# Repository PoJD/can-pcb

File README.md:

# can-pcb
Custom PCBs to be used for CAN bus in my home automation project
This repository contains 2 separate Eagle projects (http://www.cadsoftusa.com/) for custom PCB designed by myself to allow home automation system work with CAN BUS.

The basic idee is that there are 2 projects:

1. CanRelay
2. CanSwitch

CanRelay is a PCB that will be directly connected to the SSR relays and will consume traffic over the CAN bus (from either the webapp - hawa - or from CanSwitch) and translate that to switching output pins on that board's chip on or off. The board chip is PIC18F25K80 and is programmed through either CanRelay.X or CanSwitch.X mplab projects here: https://github.com/PoJD/can

CanSwitch is a PCB that will be present in the wall and would have 1 single input for the input switch, 1 single output for an indicator LED and would be connected to the CAN network too and transfer the toggle switch CAN messages over the wire to the CanRelay PCB to process.

Followed https://www.sparkfun.com/tutorials/110 to create custom components bought for this PCB and resulting in a custom library here: https://github.com/PoJD/eagle
Then followed https://learn.sparkfun.com/tutorials/using-eagle-schematic/adding-parts-to-a-schematic and other related guides to create the PCB in Eagle application.

https://learn.sparkfun.com/tutorials/using-eagle-board-layout#generating-gerbers and http://www.allpcb.com/sns/Gerber+File/2017-02-24_1_10_4819_Create+a+Gerber+File+with+Eagle/rpllst.html for generating Gerber files to let the PCBs get manufactured

See details of the communication protocal in that project, this is simply a project designed to have custom boards that would then be installed in the house.

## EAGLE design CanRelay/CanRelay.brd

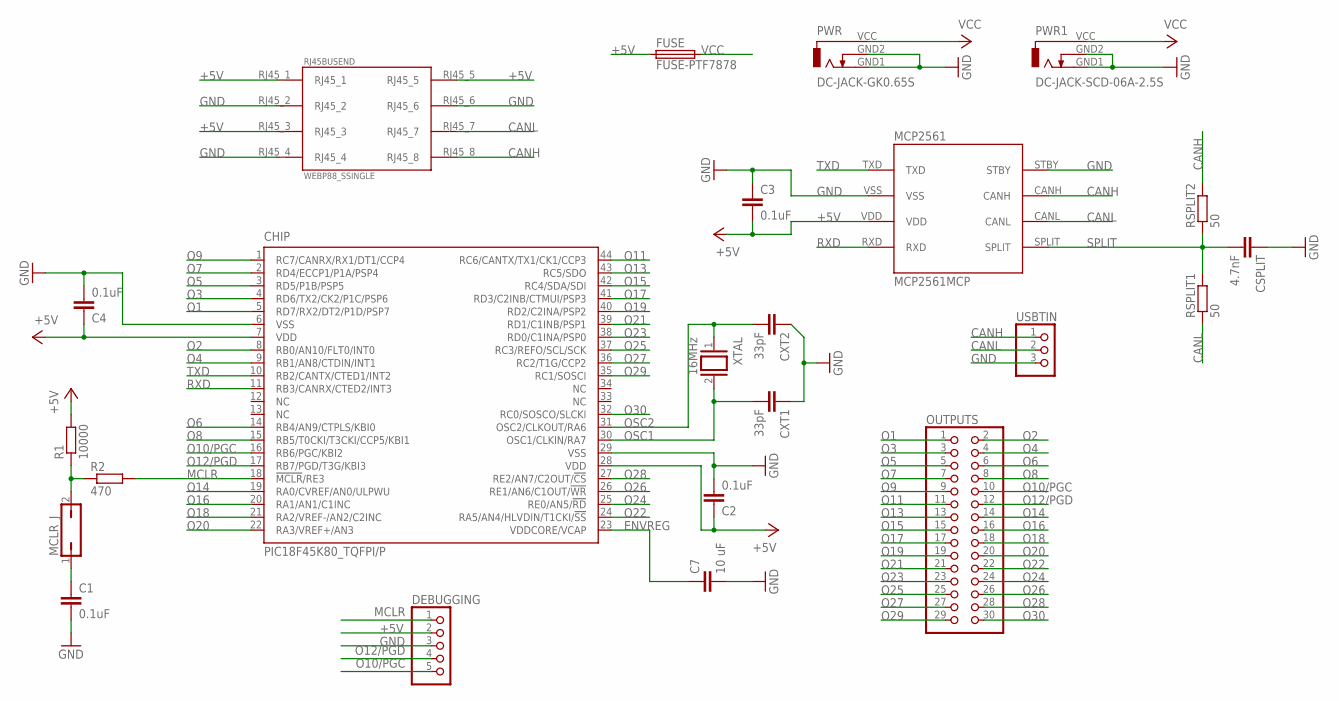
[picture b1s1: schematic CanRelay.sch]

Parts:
C1, C2, C3, C4: 0.1uF; C050-025X075
C7: 10 uF; C050-025X075
CHIP: PIC18F45K80_TQFPI/P; TQFP44
CSPLIT: 4.7nF; C050-025X075
CXT1, CXT2: 33pF; C025-030X050
DEBUGGING: PINHD-1X5; 1X05
FUSE: FUSE-PTF7878; FUSE-PTF78
MCLR_J: JP1Q; JP1
MCP2561: MCP2561MCP; MCP2561_PDIP
OUTPUTS: PINHD-2X15; 2X15
PWR: DC-JACK-GK0.65S; DC-JACK-GK0.65
PWR1: DC-JACK-SCD-06A-2.5S; DC-JACK-SCD-016A-2.5
R1: 10000; 0207/10
R2: 470; 0207/10
RJ45BUSEND: WEBP88_SSINGLE; WEBP88_RJ45_SINGLE
RSPLIT1, RSPLIT2: 50; 0207/10
USBTIN: PINHD-1X3; 1X03
XTAL: 16MHz; QS

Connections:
+5V: C2.1, C3.2, C4.1, CHIP.7 (VDD), CHIP.28 (VDD), DEBUGGING.2, FUSE.P1 (1), MCP2561.VDD, R1.2, RJ45BUSEND.RJ45_1, RJ45BUSEND.RJ45_3, RJ45BUSEND.RJ45_5
CANH: MCP2561.CANH, RJ45BUSEND.RJ45_8, RSPLIT2.2, USBTIN.1
CANL: MCP2561.CANL, RJ45BUSEND.RJ45_7, RSPLIT1.1, USBTIN.2
ENVREG: C7.1, CHIP.23 (VDDCORE/VCAP)
GND: C1.2, C2.2, C3.1, C4.2, C7.2, CHIP.6 (VSS), CHIP.29 (VSS), CSPLIT.1, CXT1.1, CXT2.1, DEBUGGING.3, MCP2561.STBY, MCP2561.VSS, PWR.GND1, PWR.GND2, PWR1.GND1, PWR1.GND2, RJ45BUSEND.RJ45_2, RJ45BUSEND.RJ45_4, RJ45BUSEND.RJ45_6, USBTIN.3
MCLR: CHIP.18 (!MCLR!/RE3), DEBUGGING.1, R2.2
unnamed: C1.1, MCLR_J.1
unnamed: MCLR_J.2, R1.1, R2.1
O1: CHIP.5 (RD7/RX2/DT2/P1D/PSP7), OUTPUTS.1
O2: CHIP.8 (RB0/AN10/FLT0/INT0), OUTPUTS.2
O3: CHIP.4 (RD6/TX2/CK2/P1C/PSP6), OUTPUTS.3
O4: CHIP.9 (RB1/AN8/CTDIN/INT1), OUTPUTS.4
O5: CHIP.3 (RD5/P1B/PSP5), OUTPUTS.5
O6: CHIP.14 (RB4/AN9/CTPLS/KBI0), OUTPUTS.6
O7: CHIP.2 (RD4/ECCP1/P1A/PSP4), OUTPUTS.7
O8: CHIP.15 (RB5/T0CKI/T3CKI/CCP5/KBI1), OUTPUTS.8
O9: CHIP.1 (RC7/CANRX/RX1/DT1/CCP4), OUTPUTS.9
O10/PGC: CHIP.16 (RB6/PGC/KBI2), DEBUGGING.5, OUTPUTS.10
O11: CHIP.44 (RC6/CANTX/TX1/CK1/CCP3), OUTPUTS.11
O12/PGD: CHIP.17 (RB7/PGD/T3G/KBI3), DEBUGGING.4, OUTPUTS.12
O13: CHIP.43 (RC5/SDO), OUTPUTS.13
O14: CHIP.19 (RA0/CVREF/AN0/ULPWU), OUTPUTS.14
O15: CHIP.42 (RC4/SDA/SDI), OUTPUTS.15
O16: CHIP.20 (RA1/AN1/C1INC), OUTPUTS.16
O17: CHIP.41 (RD3/C2INB/CTMUI/PSP3), OUTPUTS.17
O18: CHIP.21 (RA2/VREF-/AN2/C2INC), OUTPUTS.18
O19: CHIP.40 (RD2/C2INA/PSP2), OUTPUTS.19
O20: CHIP.22 (RA3/VREF+/AN3), OUTPUTS.20
O21: CHIP.39 (RD1/C1INB/PSP1), OUTPUTS.21
O22: CHIP.24 (RA5/AN4/HLVDIN/T1CKI/!SS!), OUTPUTS.22
O23: CHIP.38 (RD0/C1INA/PSP0), OUTPUTS.23
O24: CHIP.25 (RE0/AN5/!RD!), OUTPUTS.24
O25: CHIP.37 (RC3/REFO/SCL/SCK), OUTPUTS.25
O26: CHIP.26 (RE1/AN6/C1OUT/!WR!), OUTPUTS.26
O27: CHIP.36 (RC2/T1G/CCP2), OUTPUTS.27
O28: CHIP.27 (RE2/AN7/C2OUT/!CS!), OUTPUTS.28
O29: CHIP.35 (RC1/SOSCI), OUTPUTS.29
O30: CHIP.32 (RC0/SOSCO/SLCKI), OUTPUTS.30
OSC1: CHIP.30 (OSC1/CLKIN/RA7), CXT1.2, XTAL.2
OSC2: CHIP.31 (OSC2/CLKOUT/RA6), CXT2.2, XTAL.1
RXD: CHIP.11 (RB3/CANRX/CTED2/INT3), MCP2561.RXD
SPLIT: CSPLIT.2, MCP2561.SPLIT, RSPLIT1.2, RSPLIT2.1
TXD: CHIP.10 (RB2/CANTX/CTED1/INT2), MCP2561.TXD
VCC: FUSE.P2 (2), PWR.VCC, PWR1.VCC

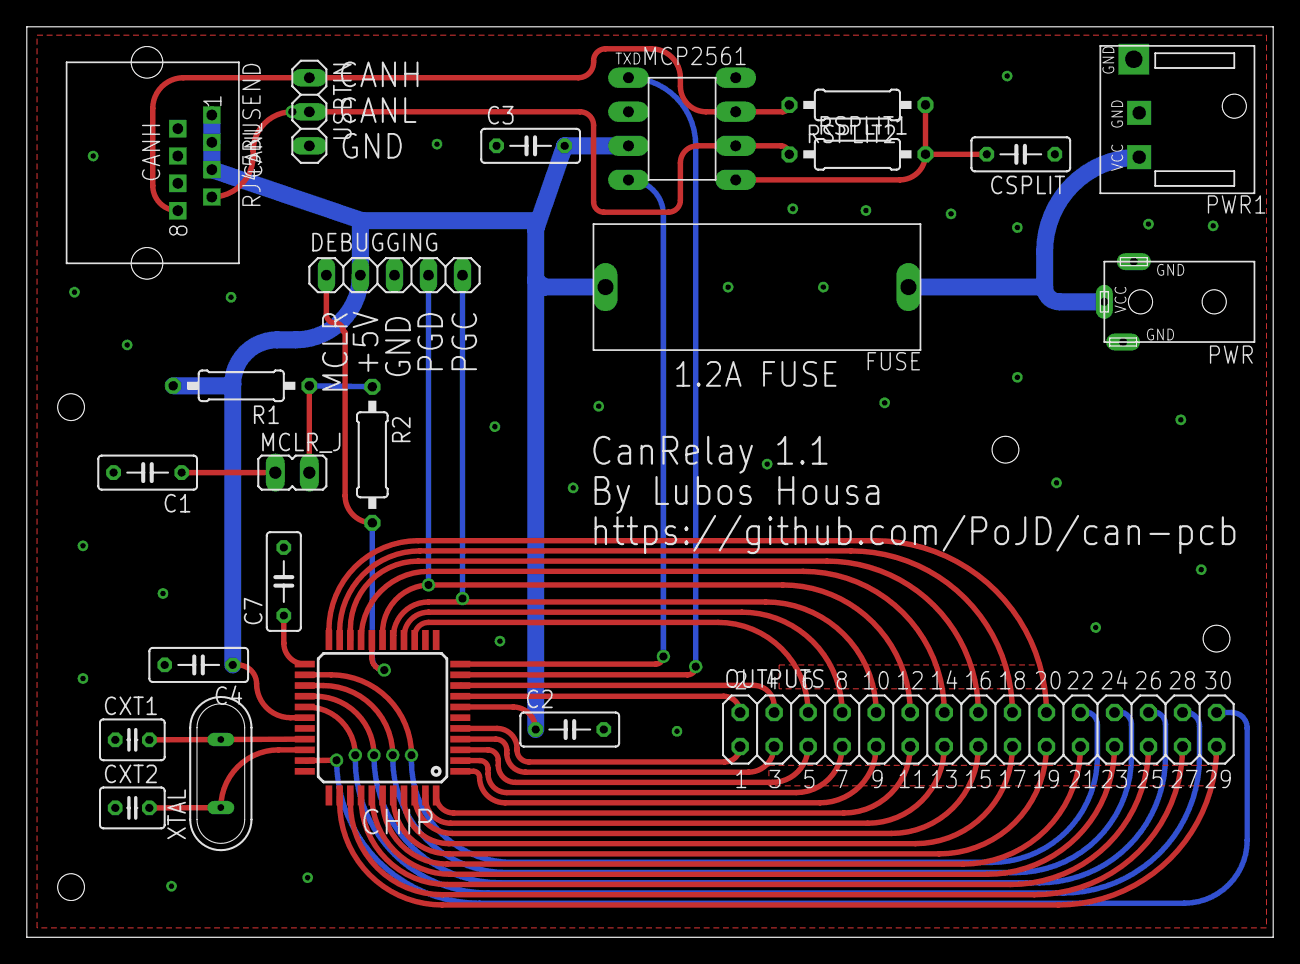
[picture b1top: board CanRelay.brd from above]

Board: 2 copper layers, 92.9 x 67.8 mm, 23 parts (0 on the bottom side), 44 nets.

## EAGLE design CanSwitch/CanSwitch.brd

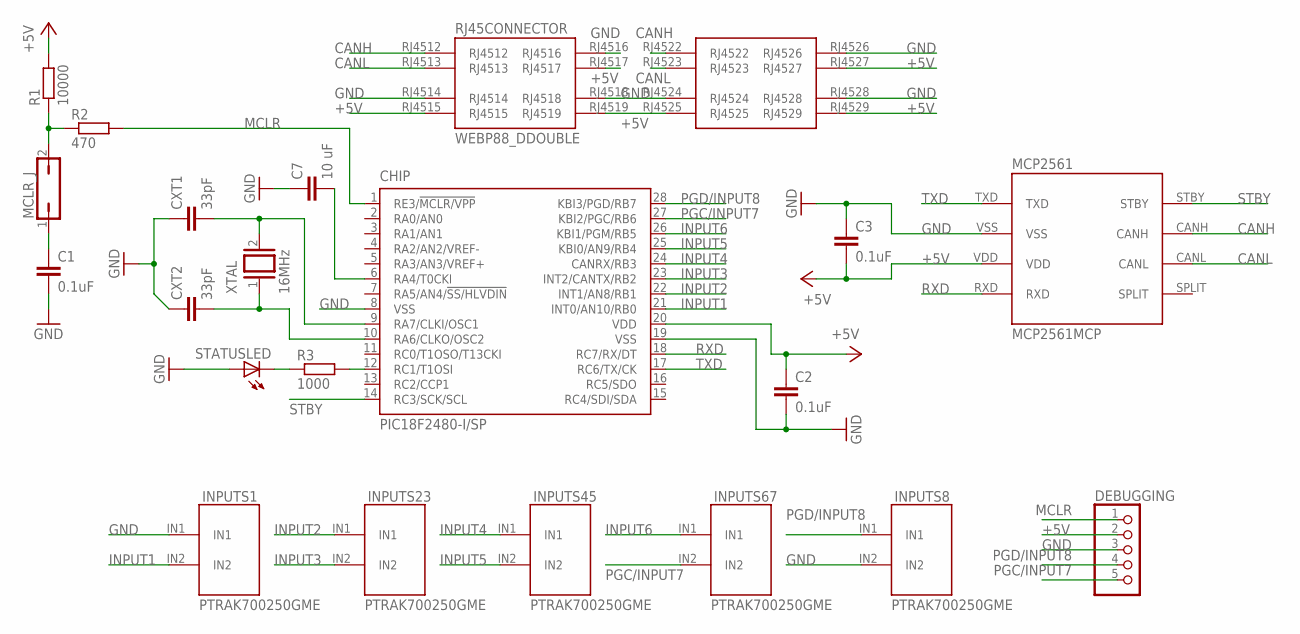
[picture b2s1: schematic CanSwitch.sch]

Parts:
C1: 0.1uF; C025-025X050
C2, C3: 0.1uF; C050-025X075
C7: 10 uF; C050-025X075
CHIP: PIC18F2480-I/SP; DIL28-3
CXT1, CXT2: 33pF; C025-030X050
DEBUGGING: PINHD-1X5; 1X05
INPUTS1, INPUTS8, INPUTS23, INPUTS45, INPUTS67: PTRAK700250GME; PTR_AK700_2_5.0
MCLR_J: JP1Q; JP1
MCP2561: MCP2561MCP; MCP2561_PDIP
R1: 10000; 0207/10
R2: 470; 0207/10
R3: 1000; 0207/10
RJ45CONNECTOR: WEBP88_DDOUBLE; WEBP88_RJ45_DOUBLE
STATUSLED: LED5MM
XTAL: 16MHz; QS

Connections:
+5V: C2.1, C3.2, CHIP.20 (VDD), DEBUGGING.2, MCP2561.VDD, R1.2, RJ45CONNECTOR.RJ4515, RJ45CONNECTOR.RJ4517, RJ45CONNECTOR.RJ4519, RJ45CONNECTOR.RJ4525, RJ45CONNECTOR.RJ4527, RJ45CONNECTOR.RJ4529
CANH: MCP2561.CANH, RJ45CONNECTOR.RJ4512, RJ45CONNECTOR.RJ4522
CANL: MCP2561.CANL, RJ45CONNECTOR.RJ4513, RJ45CONNECTOR.RJ4523
GND: C1.2, C2.2, C3.1, C7.1, CHIP.8 (VSS), CHIP.19 (VSS), CXT1.1, CXT2.1, DEBUGGING.3, INPUTS1.IN1, INPUTS8.IN2, MCP2561.VSS, RJ45CONNECTOR.RJ4514, RJ45CONNECTOR.RJ4516, RJ45CONNECTOR.RJ4518, RJ45CONNECTOR.RJ4524, RJ45CONNECTOR.RJ4526, RJ45CONNECTOR.RJ4528, STATUSLED.A
INPUT1: CHIP.21 (INT0/AN10/RB0), INPUTS1.IN2
INPUT2: CHIP.22 (INT1/AN8/RB1), INPUTS23.IN1
INPUT3: CHIP.23 (INT2/CANTX/RB2), INPUTS23.IN2
INPUT4: CHIP.24 (CANRX/RB3), INPUTS45.IN1
INPUT5: CHIP.25 (KBI0/AN9/RB4), INPUTS45.IN2
INPUT6: CHIP.26 (KBI1/PGM/RB5), INPUTS67.IN1
MCLR: CHIP.1 (RE3/!MCLR/VPP), DEBUGGING.1, R2.2
unnamed: C1.1, MCLR_J.1
unnamed: MCLR_J.2, R1.1, R2.1
unnamed: C7.2, CHIP.6 (RA4/T0CKI)
unnamed: CHIP.12 (RC1/T1OSI), R3.2
unnamed: R3.1, STATUSLED.K (C)
OSC1: CHIP.9 (RA7/CLKI/OSC1), CXT1.2, XTAL.2
OSC2: CHIP.10 (RA6/CLKO/OSC2), CXT2.2, XTAL.1
PGC/INPUT7: CHIP.27 (KBI2/PGC/RB6), DEBUGGING.5, INPUTS67.IN2
PGD/INPUT8: CHIP.28 (KBI3/PGD/RB7), DEBUGGING.4, INPUTS8.IN1
RXD: CHIP.18 (RC7/RX/DT), MCP2561.RXD
STBY: CHIP.14 (RC3/SCK/SCL), MCP2561.STBY
TXD: CHIP.17 (RC6/TX/CK), MCP2561.TXD

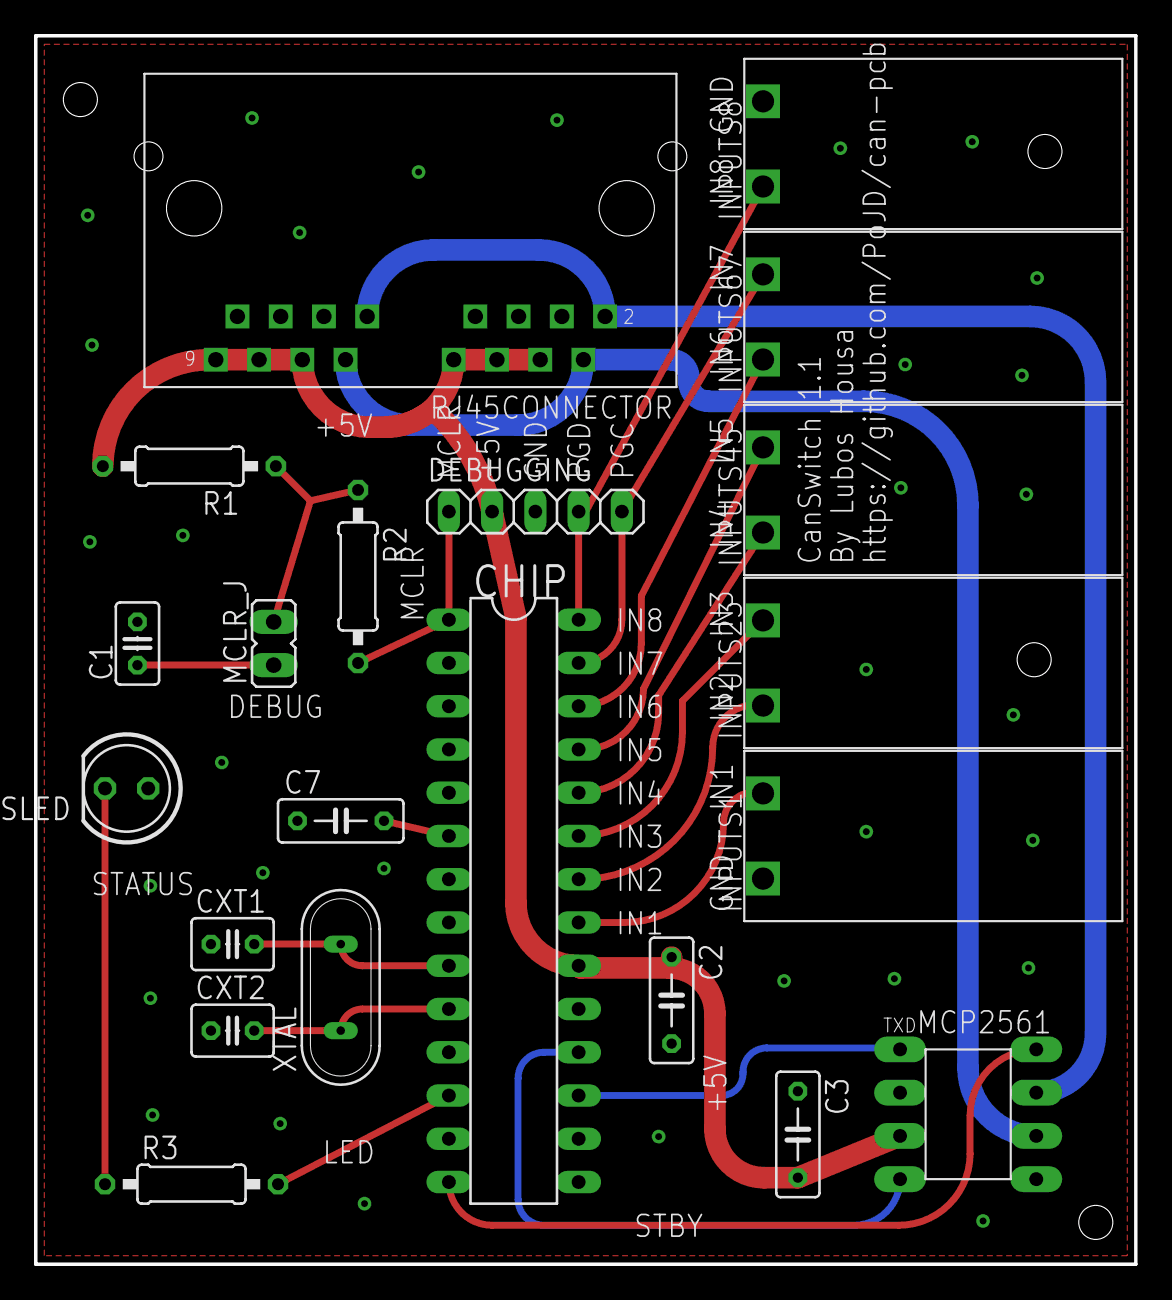
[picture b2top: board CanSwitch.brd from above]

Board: 2 copper layers, 64.6 x 72.1 mm, 21 parts (0 on the bottom side), 23 nets.

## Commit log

2016-02-21 README created
2016-02-28 initial schema for CanSwitch
2016-03-13 work in progress - just adding components so far in
2016-04-10 added all component to schema, updated library before, missing capacitors and other basic resistors and connections
2017-02-11 README updated and little tweaks to the schema
2017-02-26 wiring all up, done all in the switch with the exception of wiring up RJ45 to the rest
2017-02-26 wired up all together, no resistor or capacitor added to switch board just yet, won't be here. Now can move to PCB
2017-02-26 little edits to the schema - adding capacitors to each pair of VDD and VSS, creating first version of PCB. Missing box and proper wiring up
2017-02-27 first attempt to do proper wiring on the board
2017-02-27 backup the first version of the board
2017-11-26 cleanup after renaming libraries earlier this year and dropping auto routed nets in board to start from scratch again
2017-11-26 rerouting all, moving debugger up close to the chip, all check passed now
2017-11-26 removed extra hole from RJ45 connector
2017-11-27 swapped proper package for capacitor and also updated library components and little tweaks to the wires
2017-12-29 modified components around MCLR to be closer to the pin itself
2017-12-29 #1 added grounded copper pour around XTAL and chips
2017-12-30 #2 renamed few components, moved all to new origin, added holes for final drilling, added silkcreen to desc all, including signature. Not to print out names layers, only place and values layers in th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
2017-12-30 moving capacitor a bit further from the chip
2017-12-30 #1 dropping old polygons and replacing with full board ground polygons on both sides with isolation spacing 0.4
2017-12-30 #3 deleted backup can switch board, added new can relay base schematic as a copy from can switch, only leaving common things in there
2017-12-30 #4 adding split pin and resistor termination to can bus as per datasheet. Plus adding all wires to the chip and naming them properly
2017-12-31 #5 added outputs 20pin header from built in library. Added all the wiring to it too, missing new components that need to be added
2018-01-01 #5 new component for RJ45 WEBPP single, also renamed old one to DOUBLE and updated CanSwitch project references, used in CanRelay now and added all the wiring to it too
2018-01-01 #5 adding USBTIN 3pin connector (new component in the library)
2018-01-01 #5 adding last missing component - power jack - to the schema only. And added all wiring, ready to generate the board now
2018-01-02 first test version of the board, playing around a bit with routing, just a first sketch layout of the components on the board
2018-01-02 first draft version of the board with routed everything and copper ground too
2018-01-02 positioned all components nicely on the board and redid all wires thoroughly this time. Also replaced 3pin for usbtin by regular pinhead since that would be easier to plug into the board
2018-01-02 added some caption to silkscreen
2018-01-03 final tuning of both boards - squeezing switch board a bit yet, adding some more silkscreen, exporting to image to share on some electrical forums for checks
2018-01-04 incorporated hints from web: set proper sizes for caps, left enough space for them to be bend on the board. Reviewed any acute angles in traces. Increased isolation in ground copper so that no so cal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
2018-01-08 #6 added stitching vias to GND copper pour and some final little edits, dropping some values from some components not to spoil target PCB with extra text, checked text sizes and drill sizes, setup ER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
2018-01-11 added links to gerbers to README
2018-02-01 generating gerber files per WIKI for both designs
2018-02-01 regenerating gerbers with better job spec from Eagle direcly
2018-02-04 updating exported Gerbers
2018-09-09 #11 fixing RJ45 connector - connecting unused pins to +5V and GND
2018-09-09 #13 connect RC3 of chip and STBY of transceiver, no route yet in board until the new inputs are added
2018-09-09 #8 support for 8 independent inputs - dropped old switch input and replaced with RJ45 connector - moved components around, moved transceiver down to the bottom and the new RJ45 in the middle close to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
2018-09-10 #8 fine tuning RJ45 connections on the board - clearance errors fixed, moved components a tiny bit more, transceiver so that both CAN lines can be routed on the rights from the inputs and bottom laye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
2018-09-13 #12 dropping 2 new power jacks into the schematic and connecting. Only dropping into the board, not yet aligning up all
2018-09-15 #12 dropping the 2 and replacing with jut 1 new power jack, aliging all in board, not yet wiring all up since will need one more change to mirror the RJ45 connector anyway. but space now sufficient f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
2018-09-15 #10 mirroring pins on RJ45 and wiring up remainder to +5V and GND in schematic. Started work in board - rewired all +5V in thicker wire everywhere. wired up RJ45 +5V and GND pins, CAN lines and RX an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
2018-09-16 #10 rerouting unwired connections, moving old power jack a bit lower to have more space for the actual jack plug. routed TXD and RXD too. Missing checking all at home with the actual plug sizes, addi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
2018-09-16 #10 adding more missing GND vias to the board, running checks, adding missing labels in schematic, done #
2018-09-16 fine tuning can switch
2018-09-16 #16 adding new FUSE component - created before a new simple component from GME and added to schema now - wired up all, created new signal, used VCC for name and label +5V-RAW - this is the actual pow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
2018-09-17 little tweaks on CanRelay - aligning more labels, adding new labels to bottom silk screen, adding more vias. ready for manufacturing!
2018-09-17 opened file updated
2018-09-17 #12 fixing rectangle holes in new power connector to use dimension layer instead of rectangle in holes layer to assure these holes are really drilled
2018-09-18 fine tuning can switch - adding labels to new inputs, increased spacing of top ground copper
2018-09-18 final tweaks on CanRelay - moving CANH and CANL lines around transceiver as opposed to among its pads. Moved therefore 5V for transceiver to bottom layer. final tweaks of isolation of both ground pla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
2018-09-18 #17 replaced RJ45 for inputs with 5 PTR 2pins - RJ45 dropped and up to 5 individual PTR inputs I already bought added to the board so that they can be connected if needed - has the advantage of simpl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
2018-09-20 #17 fine tuning new input switches - added labels, updated few wires, ready to go
2018-09-21 little tweaks of labels to be more visible on target board - just the DEBUGGING part
2018-09-23 #19 dropped old chip, put new chip from eagle library on the schematic. put all mandatory connections to the chip so far only, so one more capacitor since this variant has 2 pairs of VSS and VDD pins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
2018-09-24 #19 connected all but output ports, including RXD and TXD on both schema and the board, with no erc errors. Rotated the chip in the end to get MCLR and programming up and RX and TX closer to the tran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
2018-09-26 #19 started connecting output ports. Bottom pat all done, also labeled properly, moved the whole PCB a few mms up to make space for routes there
2018-09-27 #19 wired all up. Rewired bottom part a bit too to avoid clearance errors, rather more space down there. Also rewired +5V a bit close to MCLR resistor. Also routed RXD and TXD and PGC and PGD and cho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
2018-09-28 #19 final changes after new chip - added labels to the output pinheader - added new cutout areas in top copper near the output pinheader to avoid ground copper antenna fingers in there - rewired MCLR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
2018-09-28 #20 XTAL copper is OK actually, makes no sense to isolate isolation around the pins anyway. So just added more GND vias and some new labels and moved FUSE label a bit too
2018-09-29 #21 decreasing drill size from 1 to 0.8 inline in all schema and boards for all pinhead components (debugging, usbtin and outputs in relay), so cannot now update all libraries anymore, but easier tha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
2018-09-29 #21 decreasing drill size from 0.8 to 0.7 inline in all schema and boards for all resistors
2018-09-29 #21 decreasing drill size from 0.8 to 0.6 inline in all schema and boards for all capacitors
2018-09-29 #21 decreasing drill size from 0.6 to 0.5 inline in all schema and boards for XTALs
2018-09-29 #21 decreasing drill size from 0.8 to 0.7 inline in switch for PDIP chip and in both relay and switch updated library PoJD.lbr to import new transceiver drill sizes too
2018-09-29 added two new GND vias in the middle of the output wires
2018-09-30 #21 reverting decrease in pad size for through hole transceiver and through hole chip in switch since it needs to be the original value in the end
2018-09-30 final little edits + deleting old redundant gerbes, only keeping one copy + updating cam file to the proper path to the files
2018-09-30 regenerated gerbers, moved files a bit across
